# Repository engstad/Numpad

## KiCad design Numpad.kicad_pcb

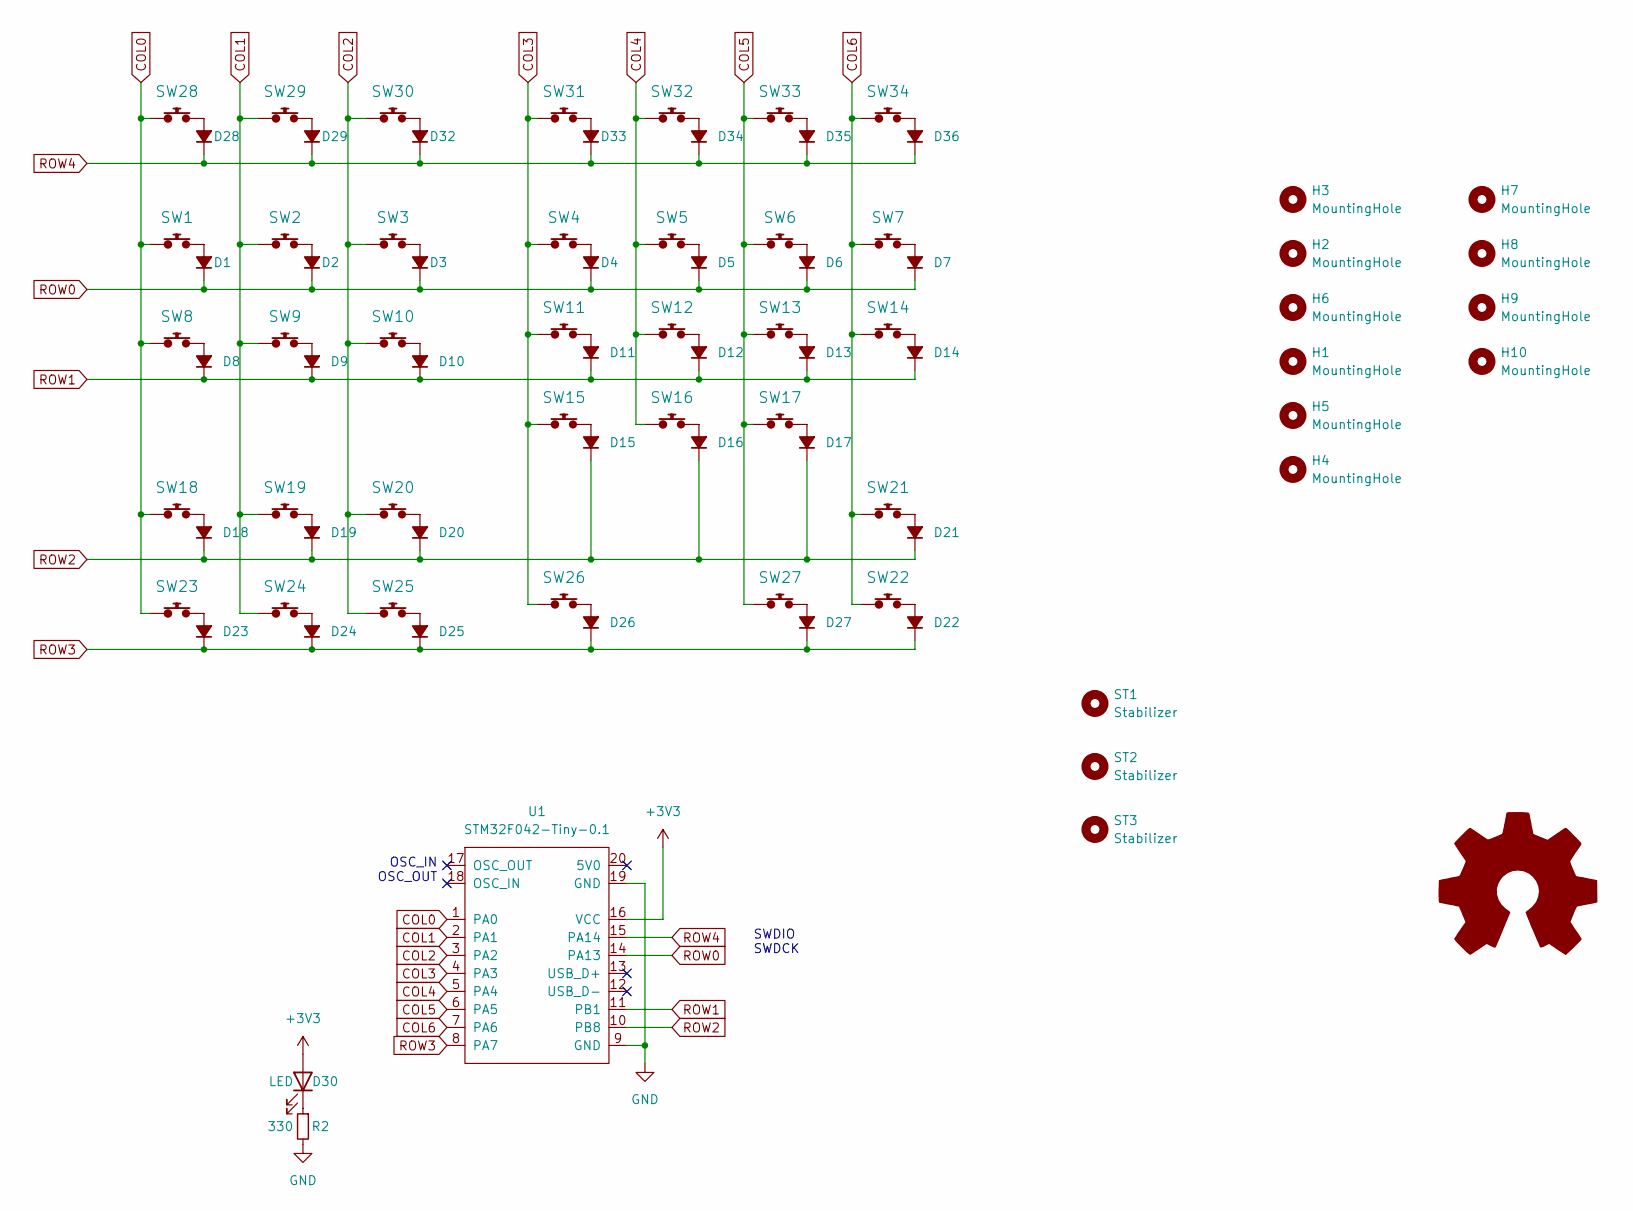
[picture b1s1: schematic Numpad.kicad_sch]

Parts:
D1, D2, D3, D4, D5, D6, D7, D8, D9, D10, D11, D12, D13, D14, D15, D16, D17, D18, D19, D20, D21, D22, D23, D24, D25, D26, D27, D28, D29, D32, D33, D34, D35, D36: D_SOD-123
D30: LED; LED_0603_1608Metric_Pad1.05x0.95mm_HandSolder
H1, H2, H3, H4, H5, H6, H7, H8, H9, H10: MountingHole; MountingHole_2.7mm_M2.5_ISO7380_Pad
R2: 330; R_0603_1608Metric_Pad0.98x0.95mm_HandSolder
ST1, ST2, ST3: Stabilizer; Stabilizer_Cherry_MX_2.00u
SW1, SW2, SW3, SW4, SW5, SW6, SW7, SW8, SW9, SW10, SW11, SW12, SW13, SW15, SW16, SW17, SW18, SW19, SW20, SW21, SW23, SW24, SW25, SW27, SW28, SW29, SW30, SW31, SW32, SW33, SW34: SW_Cherry_MX_PCB_1.00u
SW14, SW22: SW_Cherry_MX_PCB_2.00u_90deg
SW26: SW_Cherry_MX_PCB_2.00u
U1: STM32F042-Tiny-0.1; STM32F042-Tiny

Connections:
+3V3: D30.2 (A), U1.16 (VCC)
COL0: SW1.1, SW8.1, SW18.1, SW23.1, SW28.1, U1.1 (PA0)
COL1: SW2.1, SW9.1, SW19.1, SW24.1, SW29.1, U1.2 (PA1)
COL2: SW3.1, SW10.1, SW20.1, SW25.1, SW30.1, U1.3 (PA2)
COL3: SW4.1, SW11.1, SW15.1, SW26.1, SW31.1, U1.4 (PA3)
COL4: SW5.1, SW12.1, SW16.1, SW32.1, U1.5 (PA4)
COL5: SW6.1, SW13.1, SW17.1, SW27.1, SW33.1, U1.6 (PA5)
COL6: SW7.1, SW14.1, SW21.1, SW22.1, SW34.1, U1.7 (PA6)
GND: R2.2, U1.9 (GND), U1.19 (GND)
unnamed: D1.2 (A), SW1.2
unnamed: D2.2 (A), SW2.2
unnamed: D3.2 (A), SW3.2
unnamed: D4.2 (A), SW4.2
unnamed: D5.2 (A), SW5.2
unnamed: D6.2 (A), SW6.2
unnamed: D7.2 (A), SW7.2
unnamed: D8.2 (A), SW8.2
unnamed: D9.2 (A), SW9.2
unnamed: D10.2 (A), SW10.2
unnamed: D11.2 (A), SW11.2
unnamed: D12.2 (A), SW12.2
unnamed: D13.2 (A), SW13.2
unnamed: D14.2 (A), SW14.2
unnamed: D15.2 (A), SW15.2
unnamed: D16.2 (A), SW16.2
unnamed: D17.2 (A), SW17.2
unnamed: D18.2 (A), SW18.2
unnamed: D19.2 (A), SW19.2
unnamed: D20.2 (A), SW20.2
unnamed: D21.2 (A), SW21.2
unnamed: D22.2 (A), SW22.2
unnamed: D23.2 (A), SW23.2
unnamed: D24.2 (A), SW24.2
unnamed: D25.2 (A), SW25.2
unnamed: D26.2 (A), SW26.2
unnamed: D27.2 (A), SW27.2
unnamed: D28.2 (A), SW28.2
unnamed: D29.2 (A), SW29.2
unnamed: D30.1 (K), R2.1
unnamed: D32.2 (A), SW30.2
unnamed: D33.2 (A), SW31.2
unnamed: D34.2 (A), SW32.2
unnamed: D35.2 (A), SW33.2
unnamed: D36.2 (A), SW34.2
ROW0: D1.1 (K), D2.1 (K), D3.1 (K), D4.1 (K), D5.1 (K), D6.1 (K), D7.1 (K), U1.14 (PA13)
ROW1: D8.1 (K), D9.1 (K), D10.1 (K), D11.1 (K), D12.1 (K), D13.1 (K), D14.1 (K), U1.11 (PB1)
ROW2: D15.1 (K), D16.1 (K), D17.1 (K), D18.1 (K), D19.1 (K), D20.1 (K), D21.1 (K), U1.10 (PB8)
ROW3: D22.1 (K), D23.1 (K), D24.1 (K), D25.1 (K), D26.1 (K), D27.1 (K), U1.8 (PA7)
ROW4: D28.1 (K), D29.1 (K), D32.1 (K), D33.1 (K), D34.1 (K), D35.1 (K), D36.1 (K), U1.15 (PA14)

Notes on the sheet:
OSC_IN OSC_OUT
SWDIO SWDCK

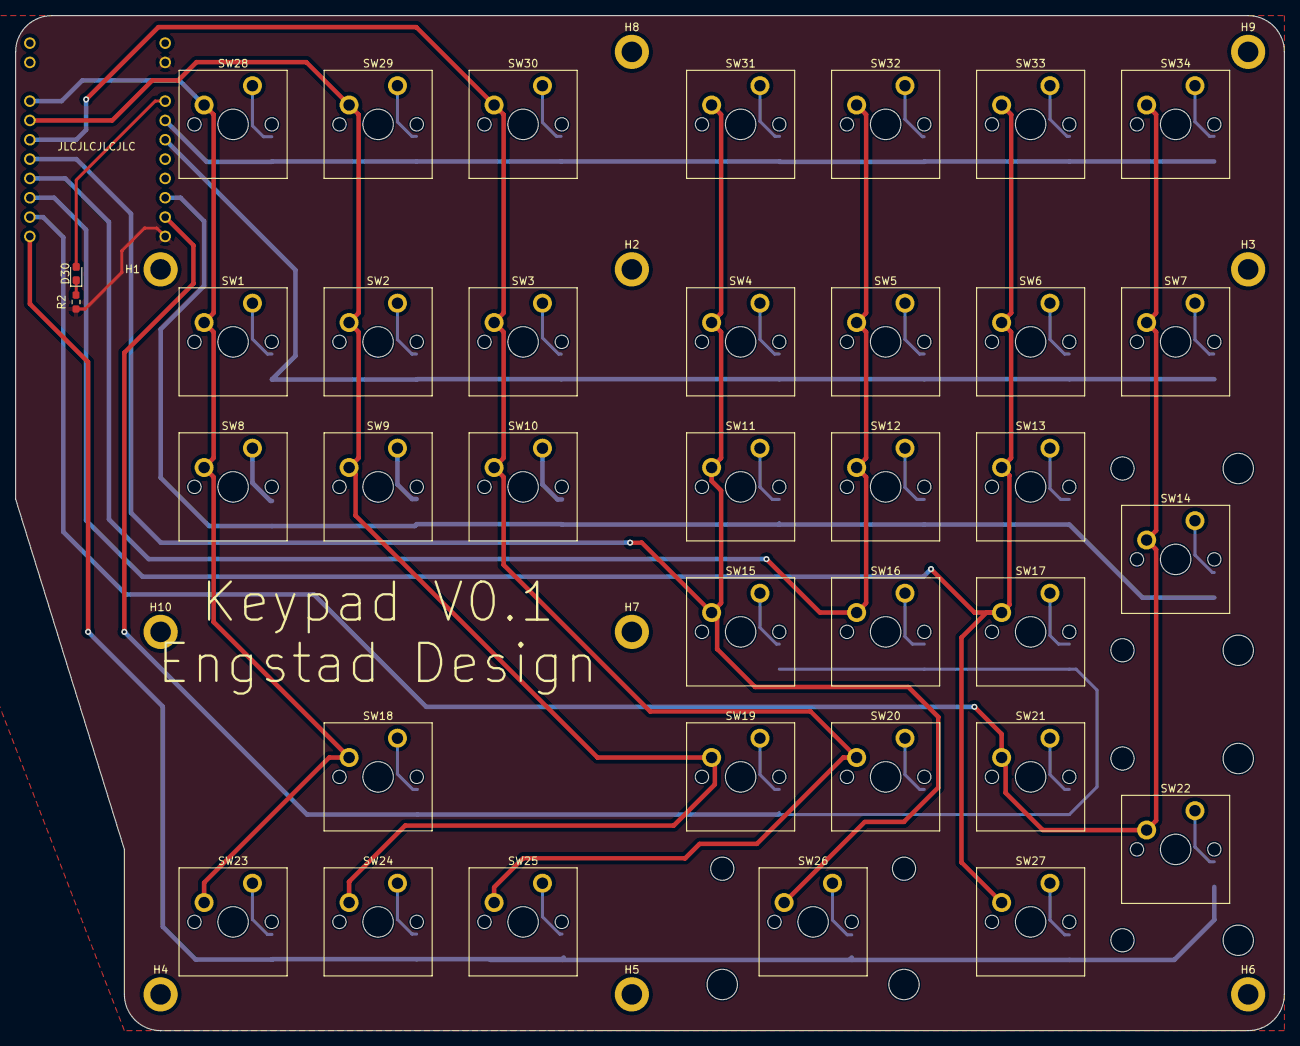
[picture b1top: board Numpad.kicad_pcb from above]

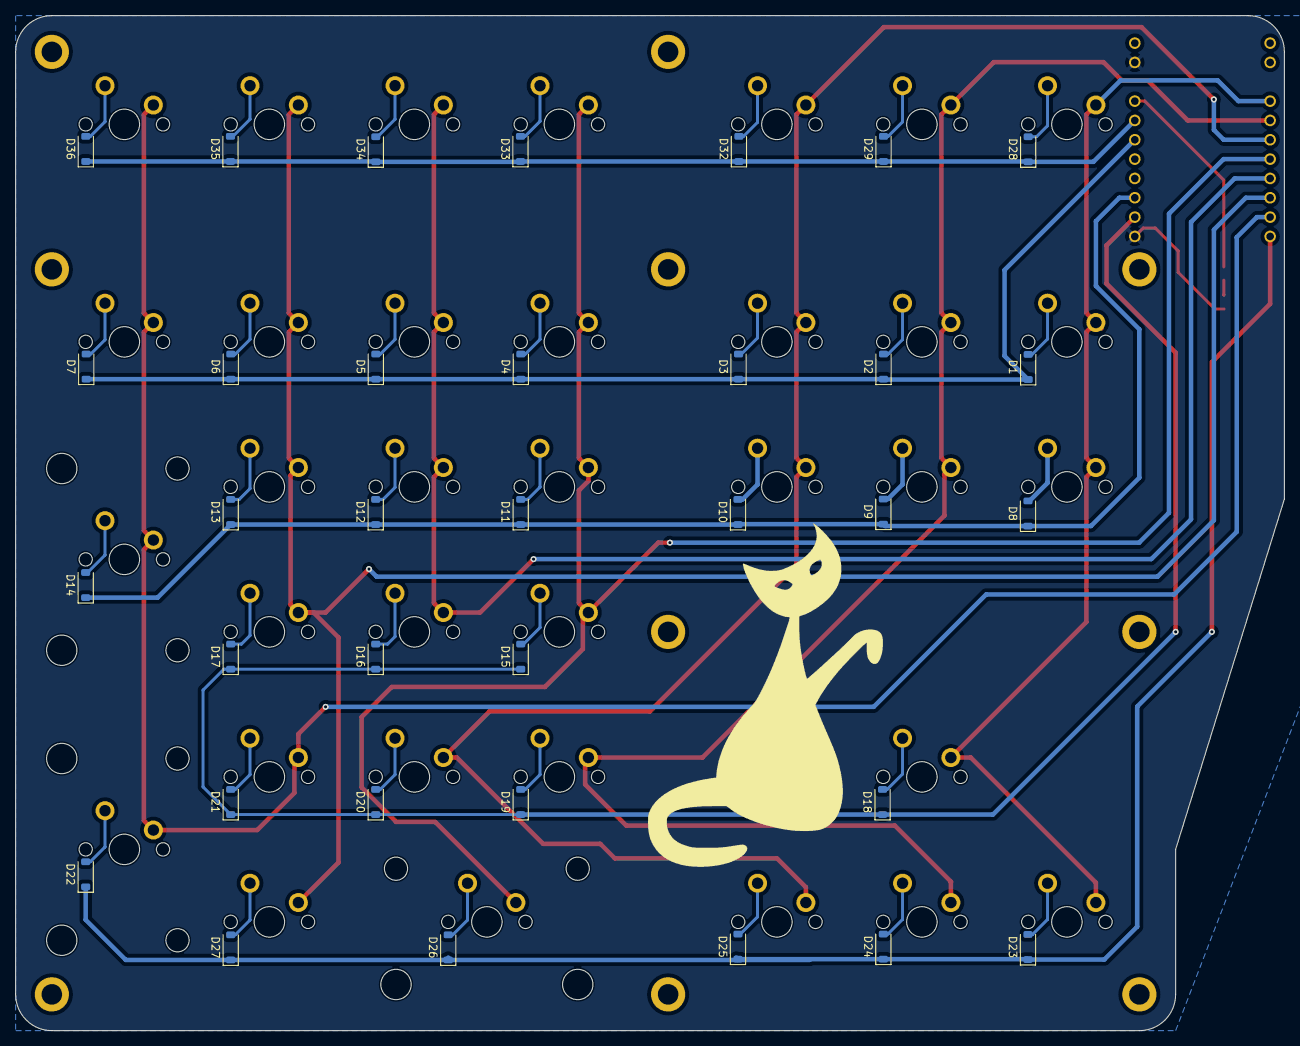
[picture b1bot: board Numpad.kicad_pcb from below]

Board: 2 copper layers, 166.7 x 133.4 mm, 84 parts (34 on the bottom side), 49 nets.

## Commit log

2024-01-12 Initial commit.
